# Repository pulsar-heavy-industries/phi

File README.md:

# What is this?

This repository hosts the source code, documentation and hardware design files for various [Pulsar Heavy Industries](http://pulsarheavyindustries.com/) projects.

There are currently 3 modules we are focusing on:
* [Cenx4](https://github.com/pulsar-heavy-industries/phi/tree/master/cenx4) - A small OLED+4 rotary encoders+other goodies modular controller.
* [Hyperion](https://github.com/pulsar-heavy-industries/phi/tree/master/hyperion) - A channel strip module, with an OLED display, 2 rotary encoders, 7 knobs, fader, and 8 LED-lit pushbuttons.
* [Narvi](https://github.com/pulsar-heavy-industries/phi/tree/master/narvi) - a 4 channel audio interface.

Our goal is to leverage technology from the last few years to push the DIY audio and MIDI controllers world forward. For more details see this series of [blog posts](http://rundste.in/tag/phi/).

# Showing off some of our prototypes

Cenx4:

Hyperion:

Narvi:

# Who is behind this?
Hi, I'm [Eran Rundstein](http://rundste.in/).

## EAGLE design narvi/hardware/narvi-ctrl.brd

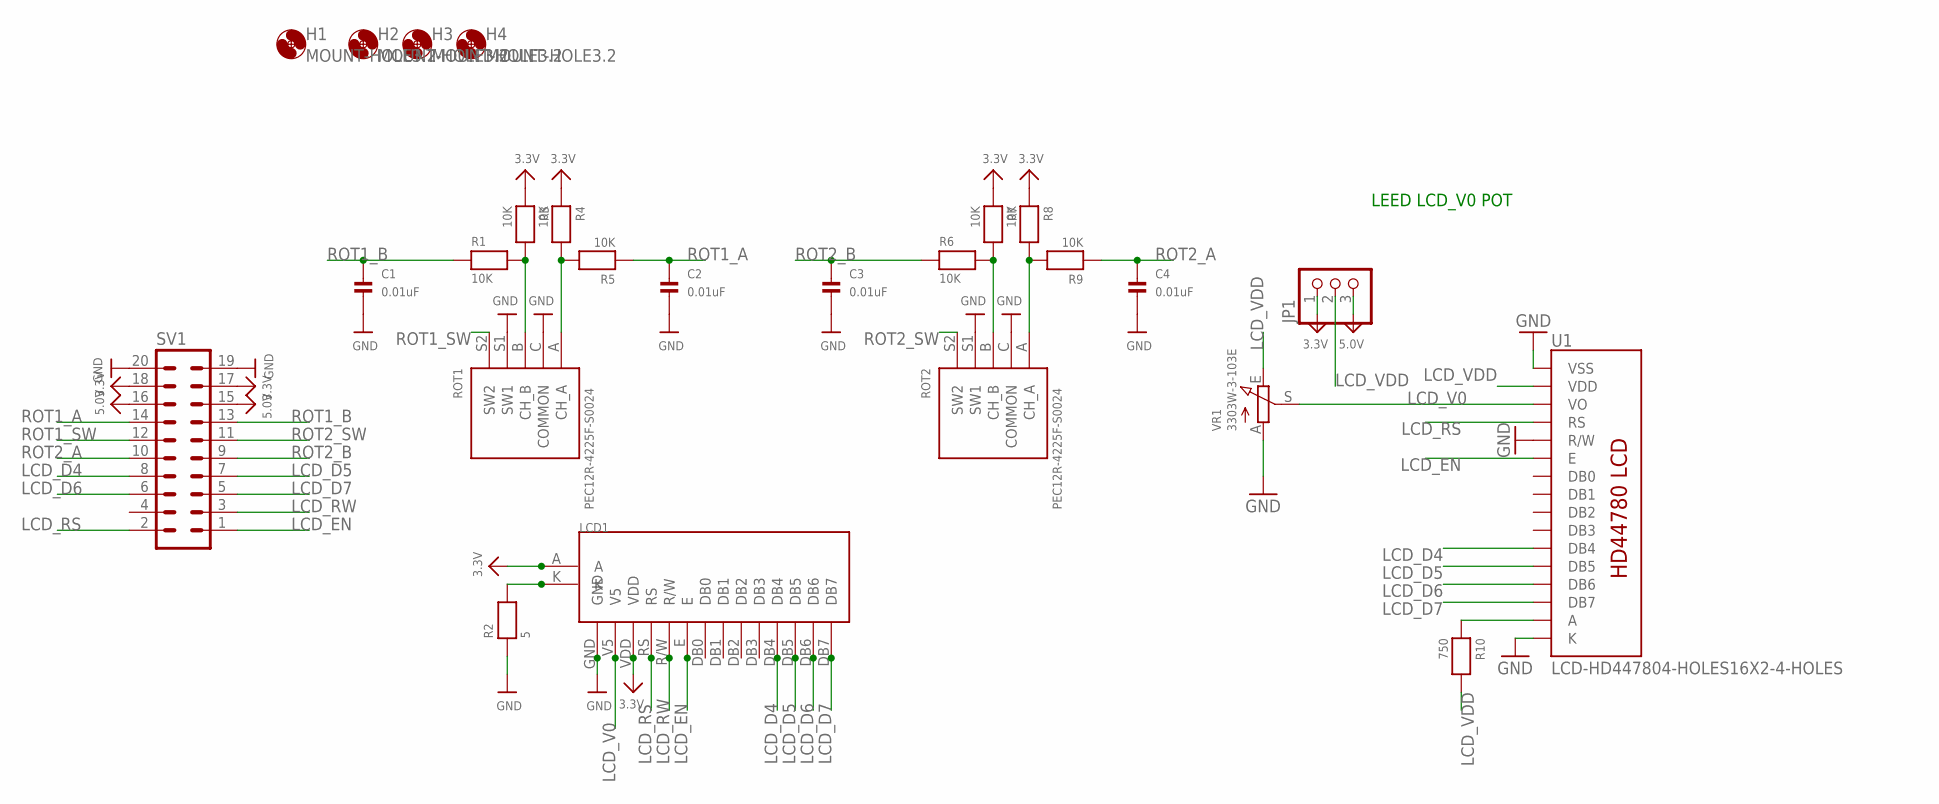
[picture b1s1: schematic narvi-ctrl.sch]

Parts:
C1, C2, C3, C4: 0.01uF; 0805
H1, H2, H3, H4: MOUNT-HOLE3.2; 3,2
JP1: PINHD-1X3; 1X03
LCD1: NHD-C0220AA-FSW-FTW
R1, R3, R4, R5, R6, R7, R8, R9: 10K; _0805
R2: 5; _0805
R10: 750; _0805
ROT1, ROT2: PEC12R-4225F-S0024; PEC111-4XXXK-SXXXX
SV1: ML203MSMT; ML20SMT; PARTNO D2520-6V0C-AR-WE
U1: LCD-HD447804-HOLES16X2-4-HOLES; LCD-16X2-4HOLES
VR1: 3303W-3-103E; TRIMPOT_BOURNS3MM

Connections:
3.3V: JP1.1, LCD1.A, LCD1.VDD, R3.1, R4.1, R7.1, R8.1, SV1.17, SV1.18
5.0V: JP1.3, SV1.15, SV1.16
GND: C1.2, C2.2, C3.2, C4.2, LCD1.GND, R2.1, ROT1.C (COMMON), ROT1.S1 (SW1), ROT2.C (COMMON), ROT2.S1 (SW1), SV1.19, SV1.20, U1.1 (VSS), U1.5 (R/W), U1.16 (K), VR1.A
LCD_D4: LCD1.DB4, SV1.8, U1.11 (DB4)
LCD_D5: LCD1.DB5, SV1.7, U1.12 (DB5)
LCD_D6: LCD1.DB6, SV1.6, U1.13 (DB6)
LCD_D7: LCD1.DB7, SV1.5, U1.14 (DB7)
LCD_EN: LCD1.E, SV1.1, U1.6 (E)
LCD_RS: LCD1.RS, SV1.2, U1.4 (RS)
LCD_RW: LCD1.R/W, SV1.3
LCD_V0: LCD1.V5, U1.3 (VO), VR1.S
LCD_VDD: JP1.2, R10.2, U1.2 (VDD), VR1.E
unnamed: LCD1.K, R2.2
unnamed: R10.1, U1.15 (A)
unnamed: R6.2, R7.2, ROT2.B (CH_B)
unnamed: R8.2, R9.2, ROT2.A (CH_A)
unnamed: R1.2, R3.2, ROT1.B (CH_B)
unnamed: R4.2, R5.2, ROT1.A (CH_A)
ROT1_A: C2.1, R5.1, SV1.14
ROT1_B: C1.1, R1.1, SV1.13
ROT1_SW: ROT1.S2 (SW2), SV1.12
ROT2_A: C4.1, R9.1, SV1.10
ROT2_B: C3.1, R6.1, SV1.9
ROT2_SW: ROT2.S2 (SW2), SV1.11

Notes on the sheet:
LEED LCD_V0 POT

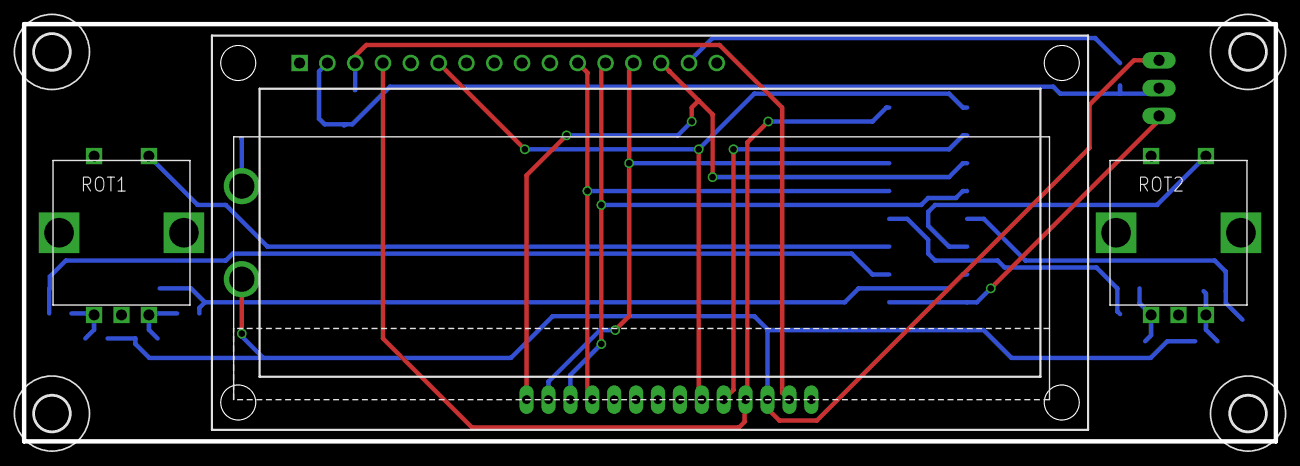
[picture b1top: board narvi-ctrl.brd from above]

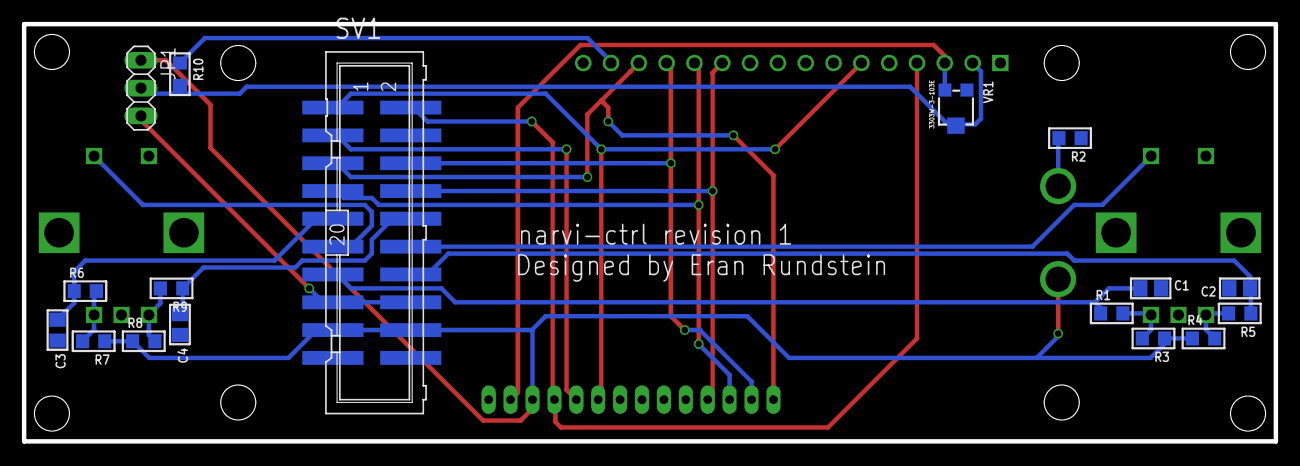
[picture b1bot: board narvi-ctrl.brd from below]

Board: 2 copper layers, 114.3 x 38.1 mm, 25 parts (17 on the bottom side), 24 nets.

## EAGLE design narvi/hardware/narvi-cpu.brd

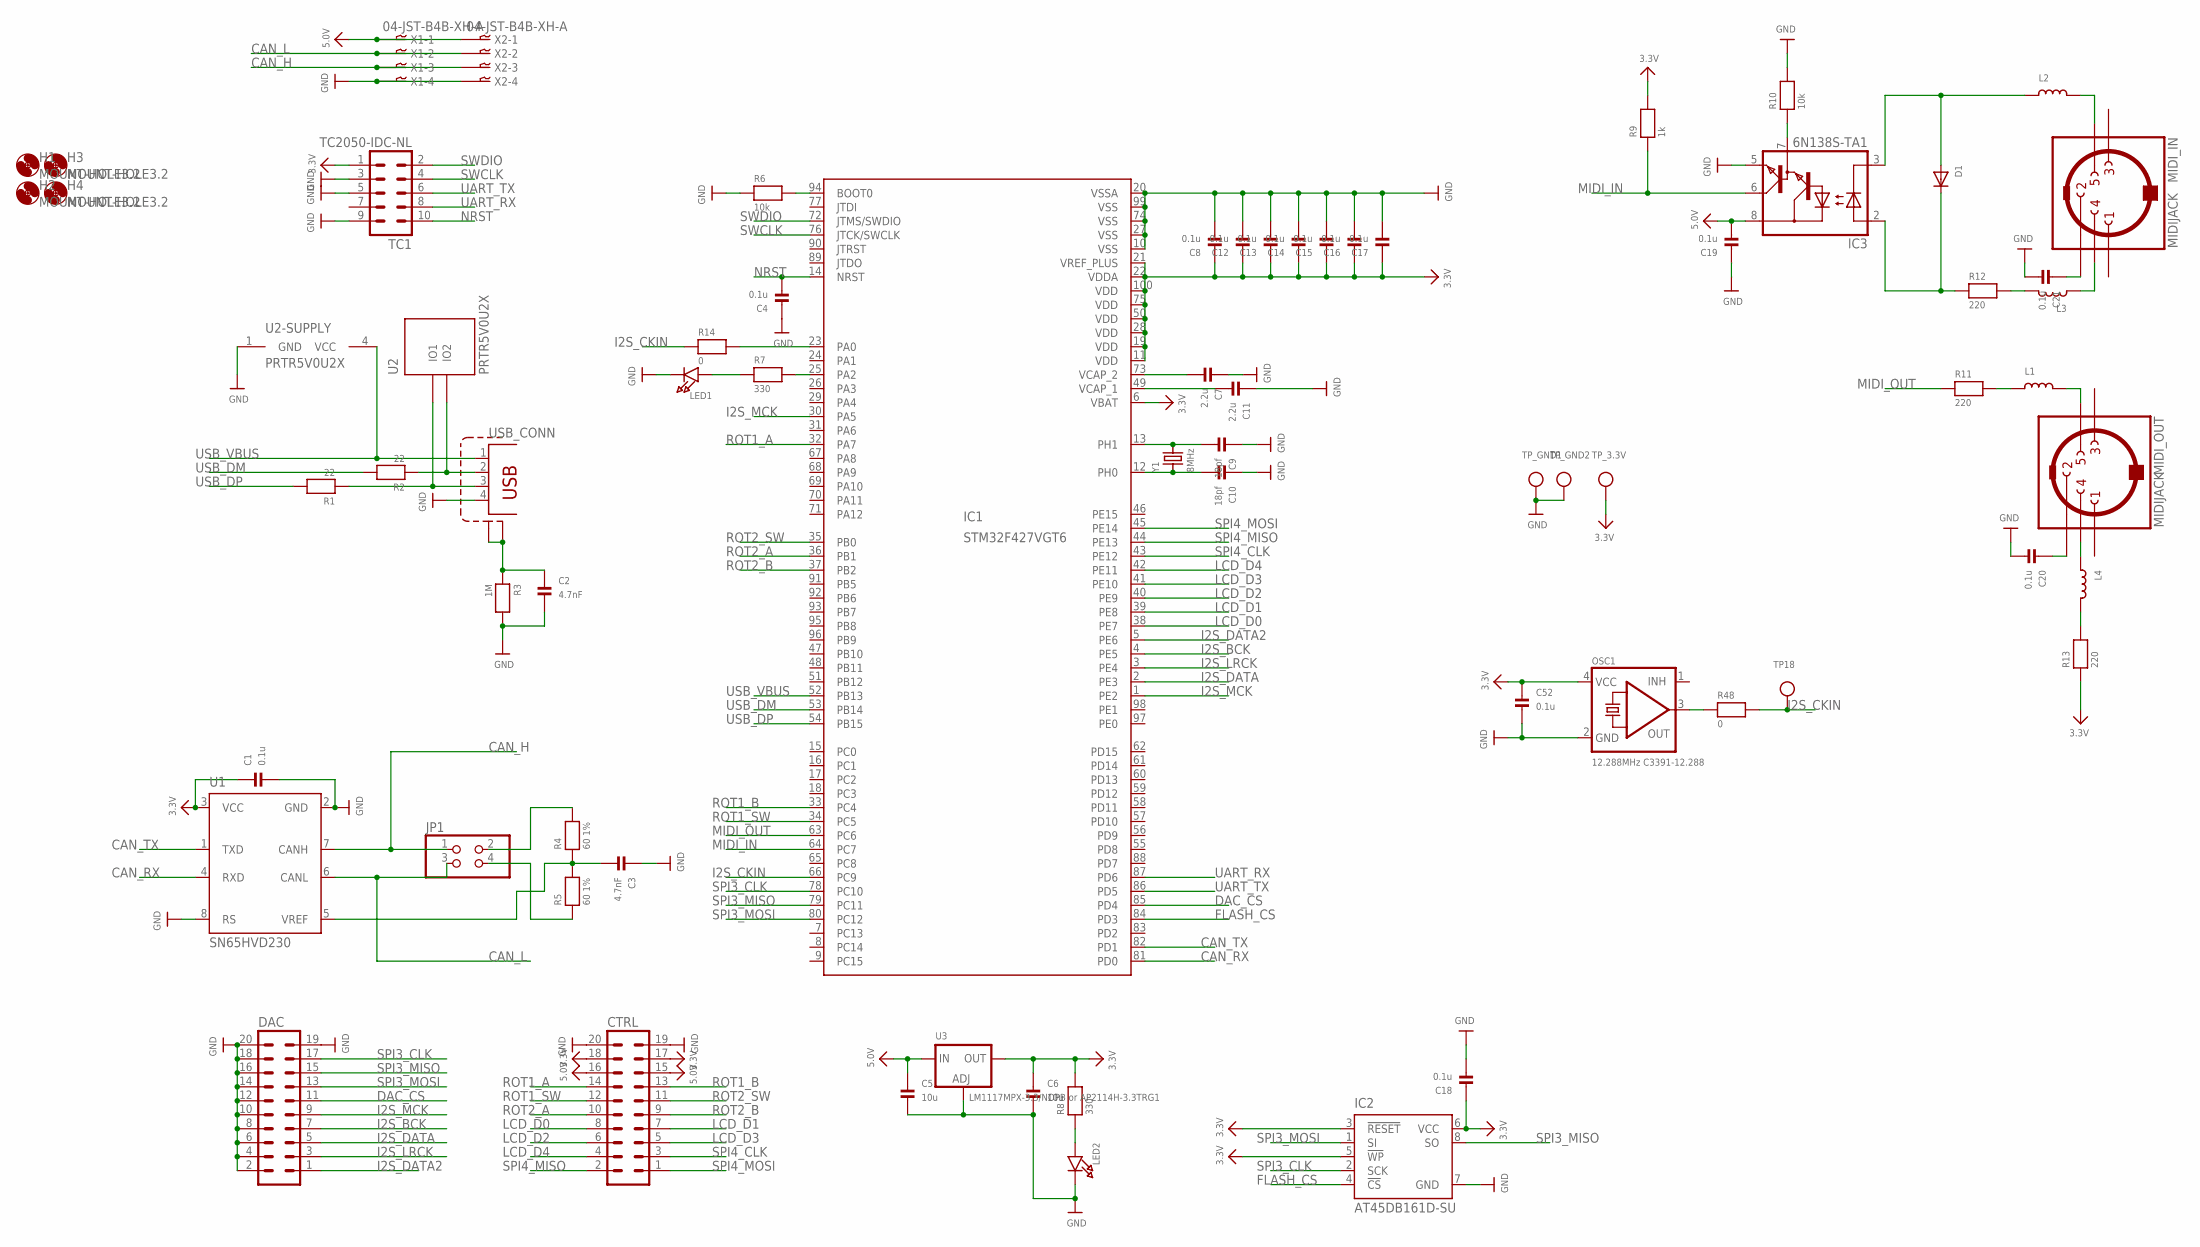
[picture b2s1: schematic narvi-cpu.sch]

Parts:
C1, C4, C8, C12, C13, C14, C15, C16, C17, C18, C19, C20, C21: 0.1u; 0603; PARTNO 0805DD104KAT2A
C2, C3: 4.7nF; 0805; PARTNO 885012207090
C5, C6: 10u; 0805; PARTNO 81-GRM21BR6YA106KE3L
C7, C11: 2.2u; 0805; PARTNO 581-08053D225MAT2A
C9, C10: 18pf; 0805; PARTNO C0805C180M3GACTU
C52: 0.1u; 0603
CTRL: ML20; PARTNO 61202021621
D1: DIODESOD-123; SOD-123; PARTNO MBR120
DAC: ML20; PARTNO 61202021621
H1, H2, H3, H4: MOUNT-HOLE3.2; 3,2
IC1: STM32F427VGT6; TQFP100; PARTNO STM32F427VGT6
IC2: AT45DB161D-SU; 8S2
IC3: 6N138S-TA1; SO8-GW300; PARTNO 6N138S
JP1: PINHD-2X2; 2X02
L1, L2, L3, L4: INDUCTOR0805; 0805; PARTNO 70-ILHB0805ER601V
LED1, LED2: LED0805; CHIPLED_0805; PARTNO 604-APT2012YC
MIDI_IN: MIDIJACK; CP-2350
MIDI_OUT: MIDIJACK; CP-2350
OSC1: 12.288MHz C3391-12.288; OSC_7X5MM
R1, R2: 22; 0805; MPN MF-RES-0603-22
R3: 1M; 0805; PARTNO AS08J1004ET
R4, R5: 60 1%; 0805; MPN MF-RES-0603-60.4
R6, R10: 10k; 0805; PARTNO RC0805FR-0710KL
R7, R8: 330; 0805; MPN MF-RES-0603-330
R9: 1k; 0805; PARTNO AS08J1001ET
R11, R12, R13: 220; 0805; PARTNO ERJ-6GEYJ221V
R14: 0; 0805; MPN MF-RES-0603-330
R48: 0; _0805
TC1: TC2050-IDC-NL
TP18: TESTPOINT0.1"; 1X01_ROUND
TP_3.3V: TESTPOINT0.1"; 1X01_ROUND
TP_GND1, TP_GND2: TESTPOINT0.1"; 1X01_ROUND
U1: SN65HVD230; SO8
U2: PRTR5V0U2X; SOT-143B
U3: LM1117MPX-3.3/NOPB or AP2114H-3.3TRG1; SOT223-R
USB: TE-292304-1
X1, X2: 04-JST-B4B-XH-A; B4B-XH
Y1: 8MHz; HC49UP; PARTNO ABLS2-8.000MHz-B1U-T

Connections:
3.3V: C1.1, C6.1, C8.1, C12.1, C13.1, C14.1, C15.1, C16.1, C17.1, C18.1, C52.1, CTRL.17, CTRL.18, IC1.6 (VBAT), IC1.11 (VDD), IC1.19 (VDD), IC1.21 (VREF_PLUS), IC1.22 (VDDA), IC1.28 (VDD), IC1.50 (VDD), IC1.75 (VDD), IC1.100 (VDD), IC2.3 (!RESET), IC2.5 (!WP), IC2.6 (VCC), OSC1.4 (VCC), R8.2, R9.2, R13.1, TC1.1, TP_3.3V.1, U1.3 (VCC), U3.2 (OUT)
5.0V: C5.1, C19.2, CTRL.15, CTRL.16, IC3.8 (VCC), U3.3 (IN), X1.P$1, X2.P$1
CAN_H: JP1.1, U1.7 (CANH), X1.P$3, X2.P$3
CAN_L: JP1.3, U1.6 (CANL), X1.P$2, X2.P$2
CAN_RX: IC1.81 (PD0), U1.4 (RXD)
CAN_TX: IC1.82 (PD1), U1.1 (TXD)
DAC_CS: DAC.11, IC1.85 (PD4)
FLASH_CS: IC1.84 (PD3), IC2.4 (!CS)
GND: C1.2, C2.2, C3.1, C4.1, C5.2, C6.2, C7.1, C8.2, C9.1, C10.1, C11.1, C12.2, C13.2, C14.2, C15.2, C16.2, C17.2, C18.2, C19.1, C20.2, C21.2, C52.2, CTRL.19, CTRL.20, DAC.2, DAC.4, DAC.6, DAC.8, DAC.10, DAC.12, DAC.14, DAC.16, DAC.18, DAC.19, DAC.20, IC1.10 (VSS), IC1.20 (VSSA), IC1.27 (VSS), IC1.74 (VSS), IC1.99 (VSS), IC2.7 (GND), IC3.5 (GND), LED1.C, LED2.C, OSC1.2 (GND), R3.2, R6.1, R10.2, TC1.3, TC1.5, TC1.9, TP_GND1.1, TP_GND2.1, U1.2 (GND), U1.8 (RS), U2.1 (GND), U3.1 (ADJ), USB.4, X1.P$4, X2.P$4
I2S_BCK: DAC.7, IC1.4 (PE5)
I2S_CKIN: IC1.66 (PC9), R14.1, R48.2, TP18.1
I2S_DATA: DAC.5, IC1.2 (PE3)
I2S_DATA2: DAC.1, IC1.5 (PE6)
I2S_LRCK: DAC.3, IC1.3 (PE4)
I2S_MCK: DAC.9, IC1.1 (PE2), IC1.30 (PA5)
LCD_D0: CTRL.8, IC1.38 (PE7)
LCD_D1: CTRL.7, IC1.39 (PE8)
LCD_D2: CTRL.6, IC1.40 (PE9)
LCD_D3: CTRL.5, IC1.41 (PE10)
LCD_D4: CTRL.4, IC1.42 (PE11)
MIDI_IN: IC1.64 (PC7), IC3.6 (VO), R9.1
MIDI_OUT: IC1.63 (PC6), R11.1
unnamed: IC1.94 (BOOT0), R6.2
unnamed: C11.2, IC1.49 (VCAP_1)
unnamed: C7.2, IC1.73 (VCAP_2)
unnamed: C9.2, IC1.13 (PH1), Y1.2
unnamed: C10.2, IC1.12 (PH0), Y1.1
unnamed: LED2.A, R8.1
unnamed: JP1.2, R4.2
unnamed: JP1.4, R5.1
unnamed: C3.2, R4.1, R5.2, U1.5 (VREF)
unnamed: IC1.25 (PA2), R7.2
unnamed: IC1.23 (PA0), R14.2
unnamed: LED1.A, R7.1
unnamed: L1.2, MIDI_OUT.5
unnamed: L1.1, R11.2
unnamed: L3.1, MIDI_IN.4
unnamed: D1.C, IC3.2 (A), R12.1
unnamed: R2.1, U2.3 (IO2), USB.2
unnamed: R1.1, U2.2 (IO1), USB.3
unnamed: C2.1, R3.1, USB.P$1 (S1), USB.P$2 (S2)
unnamed: D1.A, IC3.3 (C), L2.1
unnamed: IC3.7 (VB), R10.1
unnamed: C20.1, MIDI_OUT.2
unnamed: C21.1, MIDI_IN.2
unnamed: L2.2, MIDI_IN.5
unnamed: L3.2, R12.2
unnamed: L4.2, R13.2
unnamed: L4.1, MIDI_OUT.4
unnamed: OSC1.3 (OUT), R48.1
NRST: C4.2, IC1.14 (NRST), TC1.10
ROT1_A: CTRL.14, IC1.32 (PA7)
ROT1_B: CTRL.13, IC1.33 (PC4)
ROT1_SW: CTRL.12, IC1.34 (PC5)
ROT2_A: CTRL.10, IC1.36 (PB1)
ROT2_B: CTRL.9, IC1.37 (PB2)
ROT2_SW: CTRL.11, IC1.35 (PB0)
SPI3_CLK: DAC.17, IC1.78 (PC10), IC2.2 (SCK)
SPI3_MISO: DAC.15, IC1.79 (PC11), IC2.8 (SO)
SPI3_MOSI: DAC.13, IC1.80 (PC12), IC2.1 (SI)
SPI4_CLK: CTRL.3, IC1.43 (PE12)
SPI4_MISO: CTRL.2, IC1.44 (PE13)
SPI4_MOSI: CTRL.1, IC1.45 (PE14)
SWCLK: IC1.76 (JTCK/SWCLK), TC1.4
SWDIO: IC1.72 (JTMS/SWDIO), TC1.2
UART_RX: IC1.87 (PD6), TC1.8
UART_TX: IC1.86 (PD5), TC1.6
USB_DM: IC1.53 (PB14), R2.2
USB_DP: IC1.54 (PB15), R1.2
USB_VBUS: IC1.52 (PB13), U2.4 (VCC), USB.1

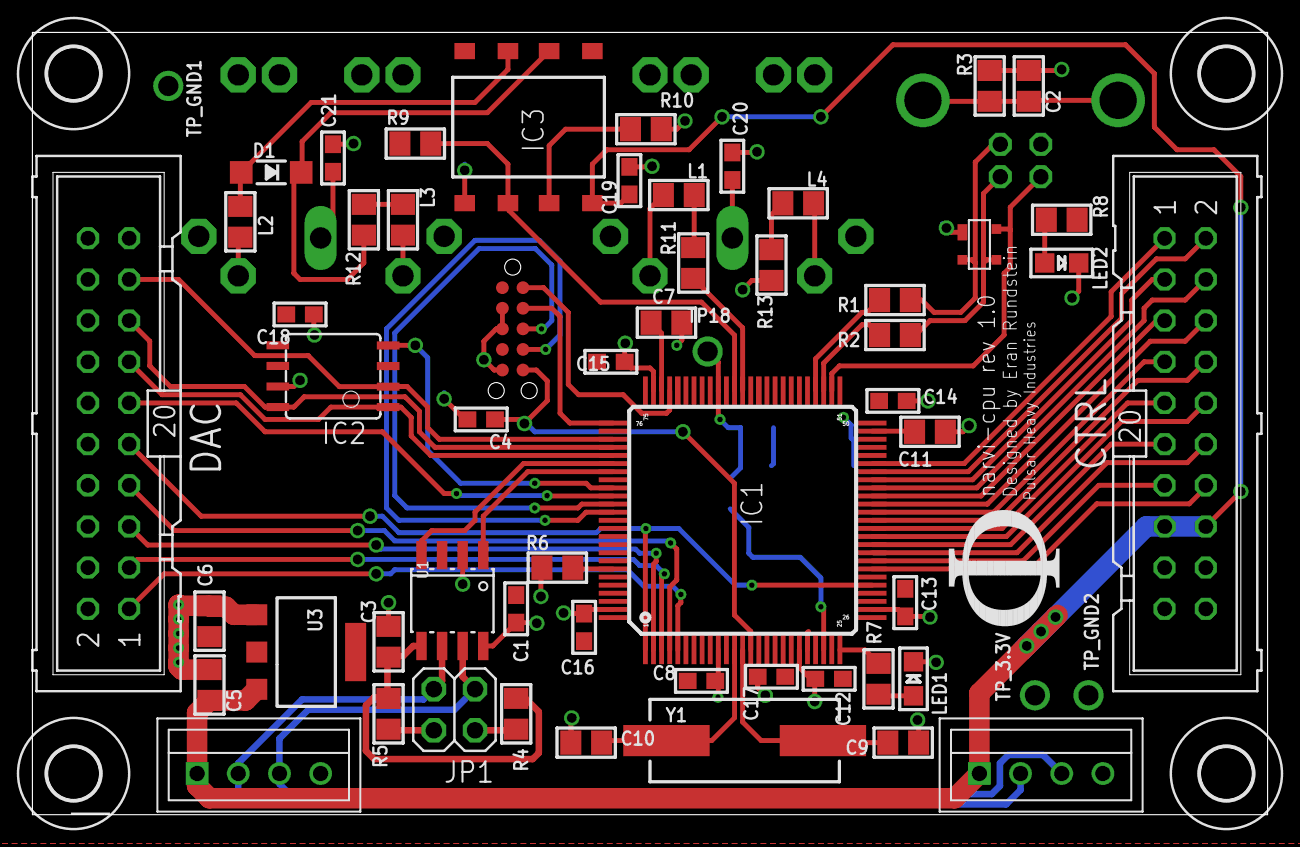
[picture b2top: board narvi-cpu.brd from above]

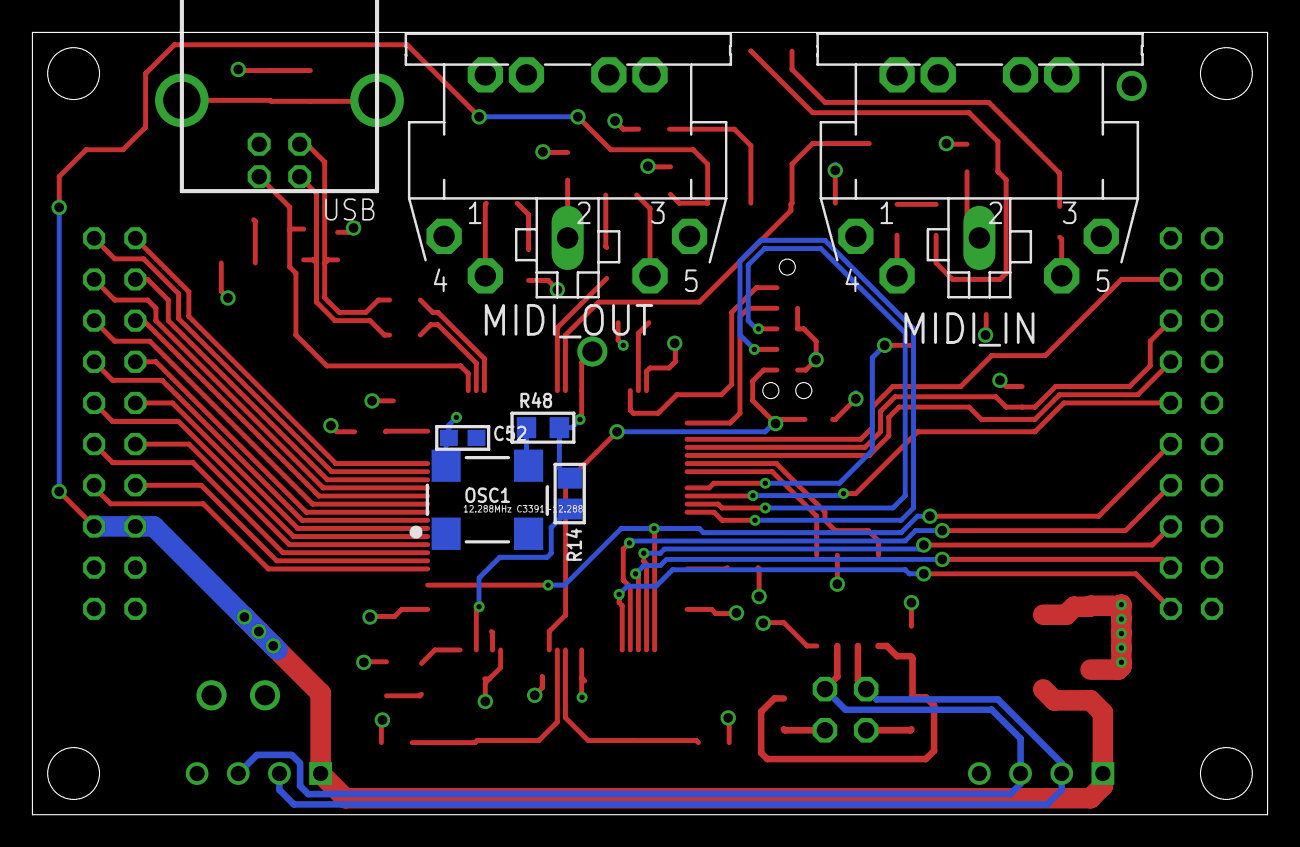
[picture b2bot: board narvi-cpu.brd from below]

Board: 2 copper layers, 76.2 x 48.3 mm, 69 parts (7 on the bottom side), 70 nets.

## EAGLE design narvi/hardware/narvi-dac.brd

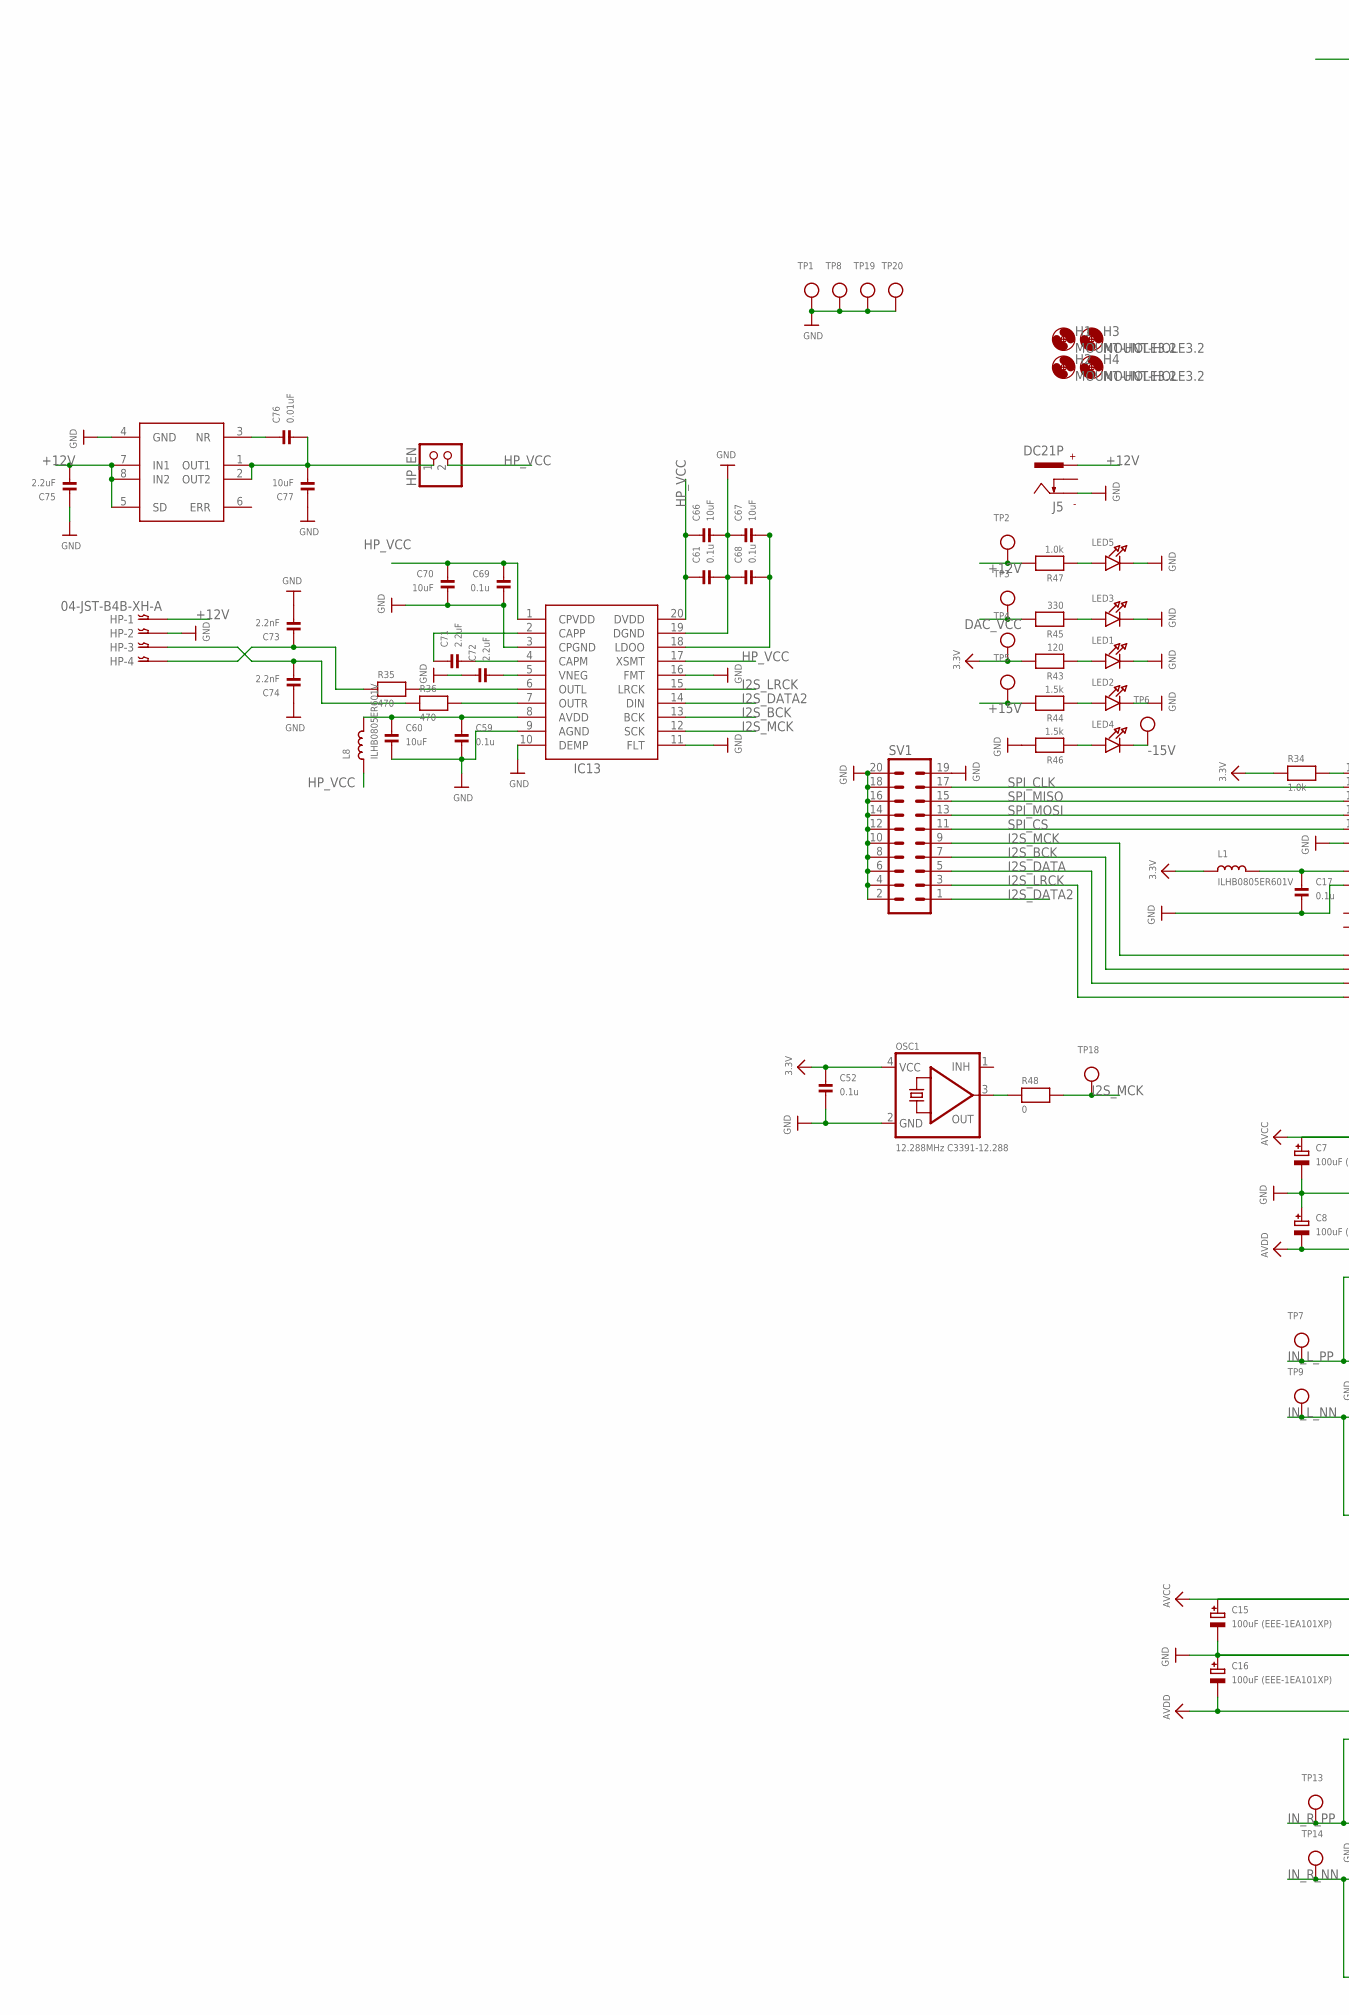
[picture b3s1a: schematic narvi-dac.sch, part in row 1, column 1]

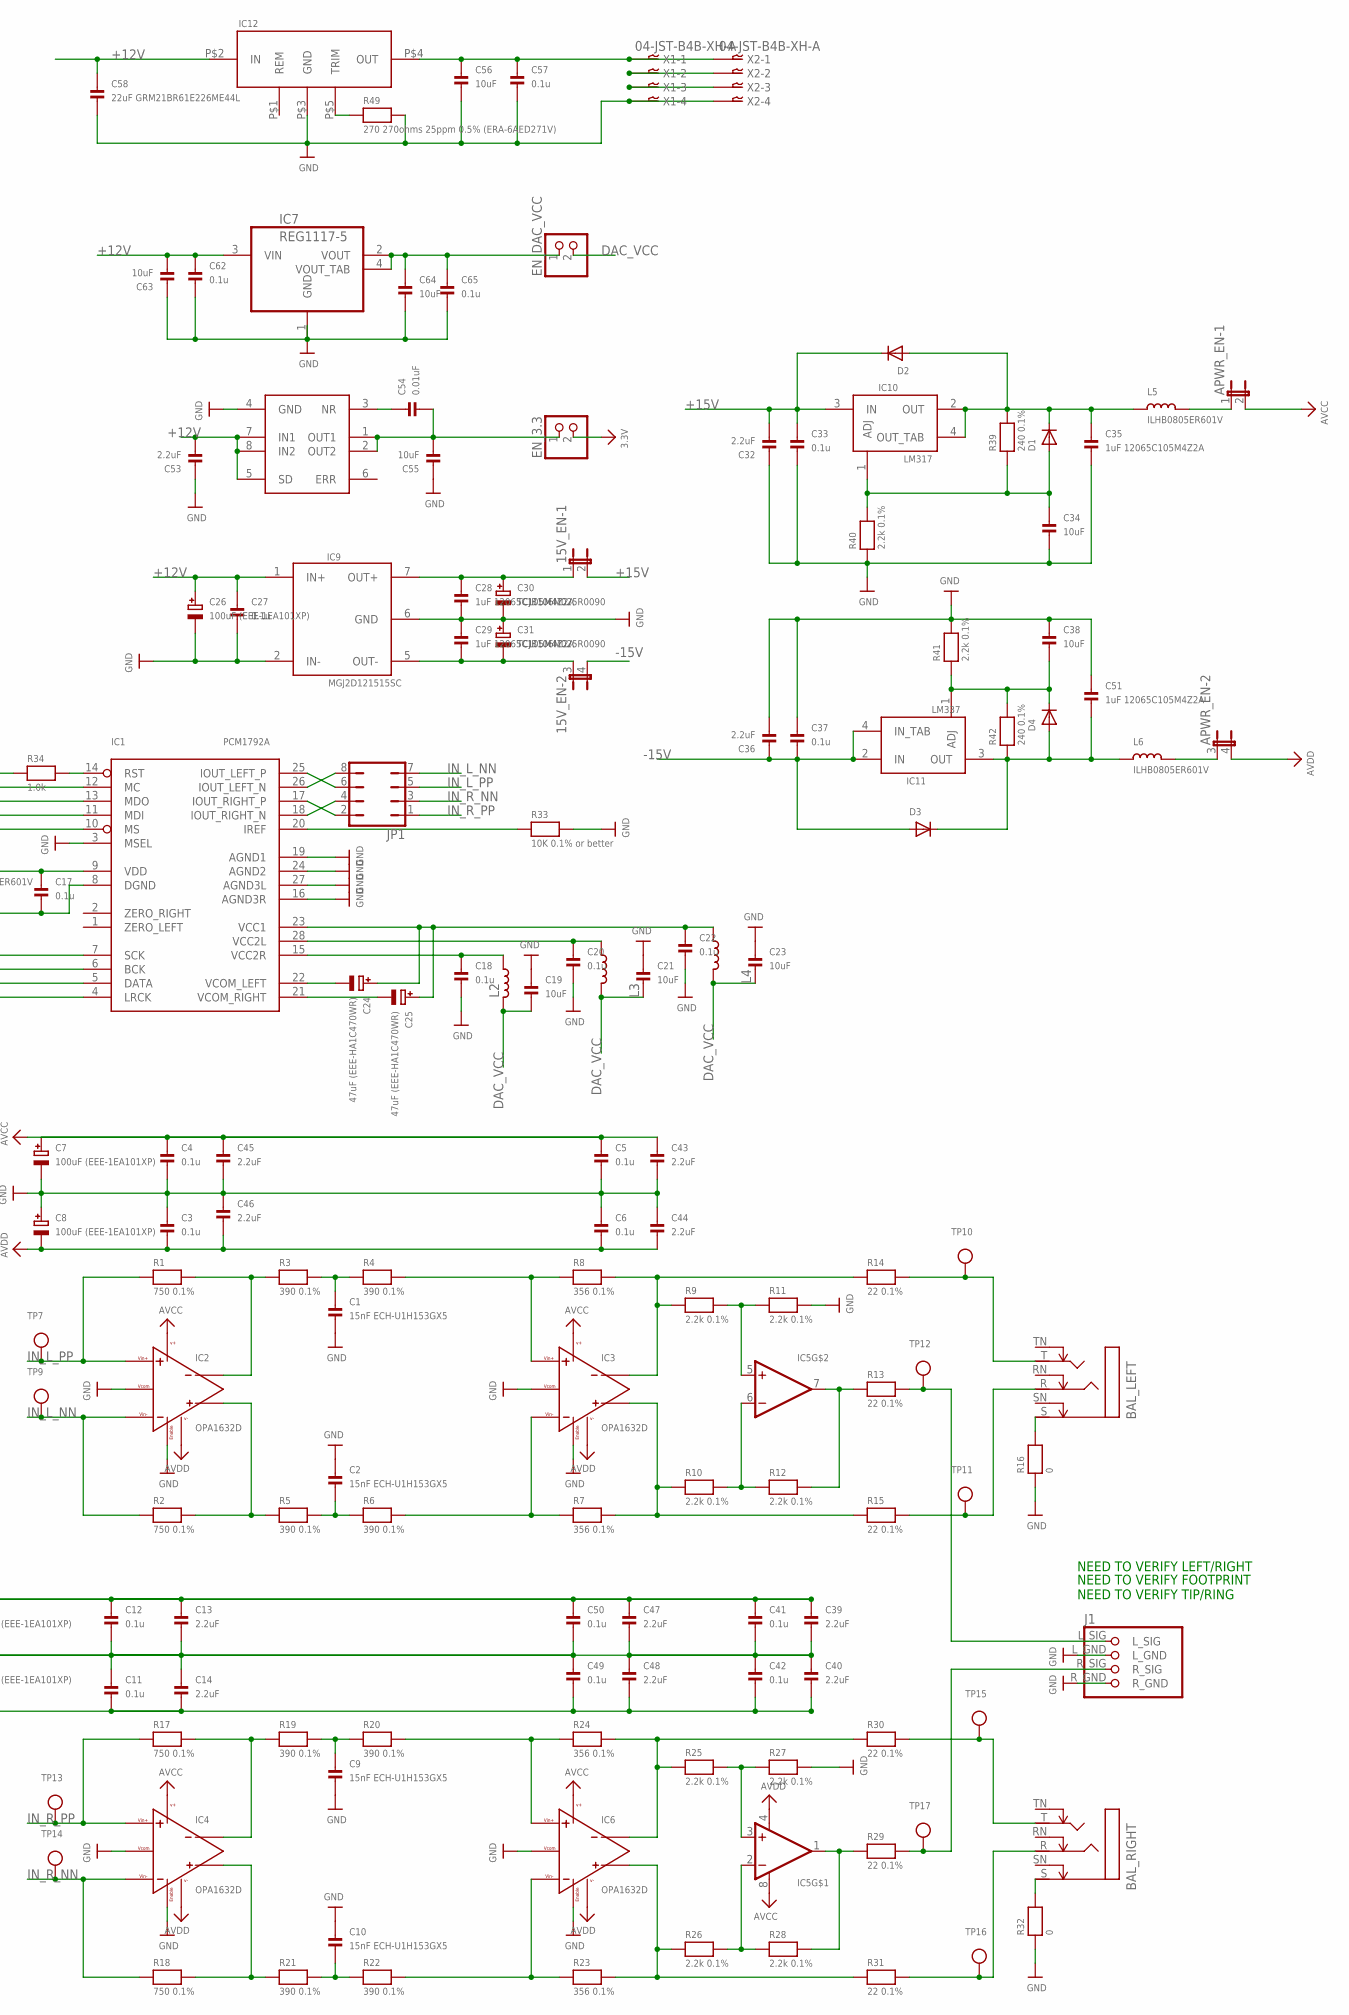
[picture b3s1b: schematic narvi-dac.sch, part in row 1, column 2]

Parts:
15V_EN: JP2QE; JP2Q
APWR_EN: JP2QE; JP2Q
BAL_LEFT: STEREOSW; NMJ6HCD2
BAL_RIGHT: STEREOSW; NMJ6HCD2
C1, C2, C9, C10: 15nF ECH-U1H153GX5; 1210
C3, C4, C5, C6, C11, C12, C17, C18, C20, C22, C27, C33, C37, C41, C42, C49, C50, C52, C57, C59, C61, C62, C65, C68, C69: 0.1u; 0603
C7, C8, C15, C16, C26: 100uF (EEE-1EA101XP); PANASONIC_D
C13, C14, C32, C36, C39, C40, C43, C44, C45, C46, C47, C48, C53, C71, C72, C75: 2.2uF; _0805
C19, C21, C23, C34, C38, C55, C56, C60, C63, C64, C66, C67, C70, C77: 10uF; 0805
C24, C25: 47uF (EEE-HA1C470WR); PANASONIC_C
C28, C29, C35, C51: 1uF 12065C105M4Z2A; 1206
C30, C31: TCJB106M025R0090; 1210POL
C54, C76: 0.01uF; 0603
C58: 22uF GRM21BR61E226ME44L; _0805
C73, C74: 2.2nF; _0805
D1, D2, D3, D4: DIODESOD-123; SOD-123
EN_3.3: HEADER-1X2; 1X02_OVAL
EN_DAC_VCC: HEADER-1X2; 1X02_OVAL
H1, H2, H3, H4: MOUNT-HOLE3.2; 3,2
HP: 04-JST-B4B-XH-A; B4B-XH
HP_EN: HEADER-1X2; 1X02_OVAL
IC1: PCM1792A; SSOP28
IC2, IC3, IC4, IC6: OPA1632D; SO08
IC5: LM4562; SOIC8_150MIL
IC7: REG1117-5; SOT223
IC8, IC14: ADP3301ARZ-3.3; SO08
IC9: MGJ2D121515SC; MURATA-MGJ2
IC10: LM317; SOT223
IC11: LM337; SOT223
IC12: MURATA_OKR-T/10-W12-C
IC13: PCM5102; TSSOP20
J1: CUI-RCJ-2123
J5: DC21P; CUI-PJ-102AH
JP1: JP4Q
L1, L2, L3, L4, L5, L6, L8: ILHB0805ER601V; _0805
LED1, LED2, LED3, LED4, LED5: LED0805; CHIPLED_0805
OSC1: 12.288MHz C3391-12.288; OSC_7X5MM
R1, R2, R17, R18: 750 0.1%; _0805
R3, R4, R5, R6, R19, R20, R21, R22: 390 0.1%; _0805
R7, R8, R23, R24: 356 0.1%; _0805
R9, R10, R11, R12, R25, R26, R27, R28, R40, R41: 2.2k 0.1%; _0805
R13, R14, R15, R29, R30, R31: 22 0.1%; _0805
R16, R32, R48: 0; _0805
R33: 10K 0.1% or better; _0805
R34, R47: 1.0k; _0805
R35, R36: 470; _0805
R39, R42: 240 0.1%; _0805
R43: 120; _0805
R44, R46: 1.5k; _0805
R45: 330; _0805
R49: 270 270ohms 25ppm 0.5% (ERA-6AED271V); _0805
SV1: ML20
TP1, TP2, TP3, TP4, TP5, TP6, TP7, TP8, TP9, TP10, TP11, TP12, TP13, TP14, TP15, TP16, TP17, TP18, TP19, TP20: TESTPOINT0.1"; 1X01_ROUND
X1, X2: 04-JST-B4B-XH-A; B4B-XH

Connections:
3.3V: C52.1, EN_3.3.2, L1.1, OSC1.4 (VCC), R34.1, R43.2, TP4.1
+12V: C26.+, C27.1, C53.2, C58.1, C62.1, C63.2, C75.2, HP.P$1, IC7.3 (VIN), IC8.5 (SD), IC8.7 (IN1), IC8.8 (IN2), IC9.1 (IN+), IC12.P$2 (IN), IC14.5 (SD), IC14.7 (IN1), IC14.8 (IN2), J5.+, R47.2, TP2.1
+15V: 15V_EN.2, C32.2, C33.1, D2.C, IC10.3 (IN), R44.2, TP5.1
-15V: 15V_EN.4 (2), C36.1, C37.2, D3.A, IC11.2 (IN), IC11.4 (IN_TAB), LED4.C, TP6.1
AVCC: APWR_EN.2, C4.1, C5.1, C7.+, C12.1, C13.1, C15.+, C39.1, C41.1, C43.1, C45.1, C47.1, C50.1, IC2.3 (V+), IC3.3 (V+), IC4.3 (V+), IC5.8 (V+), IC6.3 (V+)
AVDD: APWR_EN.4 (2), C3.2, C6.2, C8.-, C11.2, C14.2, C16.-, C40.2, C42.2, C44.2, C46.2, C48.2, C49.2, IC2.6 (V-), IC3.6 (V-), IC4.6 (V-), IC5.4 (V-), IC6.6 (V-)
CAN_H: X1.P$3, X2.P$3
CAN_L: X1.P$2, X2.P$2
DAC_VCC: C19.2, C21.2, C23.2, EN_DAC_VCC.2, L2.2, L3.2, L4.2, R45.2, TP3.1
GND: C1.2, C2.1, C3.1, C4.2, C5.2, C6.1, C7.-, C8.+, C9.2, C10.1, C11.1, C12.2, C13.2, C14.1, C15.-, C16.+, C17.2, C18.2, C19.1, C20.2, C21.1, C22.2, C23.1, C26.-, C27.2, C28.2, C29.1, C30.2- (-), C31.1+ (+), C32.1, C33.2, C34.2, C35.2, C36.2, C37.1, C38.1, C39.2, C40.1, C41.2, C42.1, C43.2, C44.1, C45.2, C46.1, C47.2, C48.1, C49.1, C50.2, C51.1, C52.2, C53.1, C55.1, C56.2, C57.2, C58.2, C59.2, C60.2, C61.2, C62.2, C63.1, C64.2, C65.2, C66.2, C67.1, C68.1, C69.2, C70.2, C72.1, C73.2, C74.1, C75.1, C77.1, HP.P$2, IC1.3 (MSEL), IC1.8 (DGND), IC1.16 (AGND3R), IC1.19 (AGND1), IC1.24 (AGND2), IC1.27 (AGND3L), IC2.2 (VCOM), IC2.7 (ENABLE), IC3.2 (VCOM), IC3.7 (ENABLE), IC4.2 (VCOM), IC4.7 (ENABLE), IC6.2 (VCOM), IC6.7 (ENABLE), IC7.1 (GND), IC8.4 (GND), IC9.2 (IN-), IC9.6 (GND), IC12.P$3 (GND), IC13.3 (CPGND), IC13.9 (AGND), IC13.10 (DEMP), IC13.11 (FLT), IC13.16 (FMT), IC13.19 (DGND), IC14.4 (GND), J1.L_GND, J1.R_GND, J5.-, LED1.C, LED2.C, LED3.C, LED5.C, OSC1.2 (GND), R11.2, R16.1, R27.2, R32.1, R33.2, R40.1, R41.2, R46.2, R49.2, SV1.2, SV1.4, SV1.6, SV1.8, SV1.10, SV1.12, SV1.14, SV1.16, SV1.18, SV1.19, SV1.20, TP1.1, TP8.1, TP19.1, TP20.1, X1.P$4, X2.P$4
HP_L_OUT: C73.1, HP.P$4, R35.1
HP_R_OUT: C74.2, HP.P$3, R36.1
HP_VCC: C61.1, C66.1, C69.1, C70.1, HP_EN.2, IC13.1 (CPVDD), IC13.17 (XSMT), IC13.20 (DVDD), L8.1
I2S_BCK: IC1.6 (BCK), IC13.13 (BCK), SV1.7
I2S_DATA: IC1.5 (DATA), SV1.5
I2S_DATA2: IC13.14 (DIN), SV1.1
I2S_LRCK: IC1.4 (LRCK), IC13.15 (LRCK), SV1.3
I2S_MCK: IC1.7 (SCK), IC13.12 (SCK), R48.2, SV1.9, TP18.1
IN_L_NN: IC2.1 (VIN-), JP1.7, R2.1, TP9.1
IN_L_PP: IC2.8 (VIN+), JP1.5, R1.1, TP7.1
IN_R_NN: IC4.1 (VIN-), JP1.3, R18.1, TP14.1
IN_R_PP: IC4.8 (VIN+), JP1.1, R17.1, TP13.1
unnamed: IC2.5 (VOUT-), R1.2, R3.1
unnamed: IC2.4 (VOUT+), R2.2, R5.1
unnamed: C1.1, R3.2, R4.1
unnamed: C2.2, R5.2, R6.1
unnamed: IC3.8 (VIN+), R4.2, R8.1
unnamed: IC3.1 (VIN-), R6.2, R7.1
unnamed: IC1.17 (IOUT_RIGHT_P), JP1.2
unnamed: IC1.18 (IOUT_RIGHT_N), JP1.4
unnamed: IC5.5 (+IN), R9.2, R11.1
unnamed: IC5.6 (-IN), R10.2, R12.1
unnamed: IC5.7 (OUT), R12.2, R13.1
unnamed: J1.L_SIG, R13.2, TP12.1
unnamed: BAL_LEFT.S, R16.2
unnamed: BAL_LEFT.T, R14.2, TP10.1
unnamed: BAL_LEFT.R, R15.2, TP11.1
unnamed: IC4.5 (VOUT-), R17.2, R19.1
unnamed: IC4.4 (VOUT+), R18.2, R21.1
unnamed: C9.1, R19.2, R20.1
unnamed: C10.2, R21.2, R22.1
unnamed: IC6.8 (VIN+), R20.2, R24.1
unnamed: IC6.1 (VIN-), R22.2, R23.1
unnamed: IC1.26 (IOUT_LEFT_N), JP1.8
unnamed: IC1.25 (IOUT_LEFT_P), JP1.6
unnamed: IC5.3 (+IN), R25.2, R27.1
unnamed: IC5.2 (-IN), R26.2, R28.1
unnamed: J1.R_SIG, R29.2, TP17.1
unnamed: BAL_RIGHT.S, R32.2
unnamed: BAL_RIGHT.T, R30.2, TP15.1
unnamed: BAL_RIGHT.R, R31.2, TP16.1
unnamed: C56.1, C57.1, IC12.P$4 (OUT), X1.P$1, X2.P$1
unnamed: OSC1.3 (OUT), R48.1
unnamed: IC12.P$5 (TRIM), R49.1
unnamed: IC5.1 (OUT), R28.2, R29.1
unnamed: IC1.20 (IREF), R33.1
unnamed: C18.1, IC1.15 (VCC2R), L2.1
unnamed: C17.1, IC1.9 (VDD), L1.2
unnamed: C20.1, IC1.28 (VCC2L), L3.1
unnamed: C22.1, C24.+, C25.+, IC1.23 (VCC1), L4.1
unnamed: C24.-, IC1.22 (VCOM_LEFT)
unnamed: C25.-, IC1.21 (VCOM_RIGHT)
unnamed: IC1.14 (RST), R34.2
unnamed: C59.1, C60.1, IC13.8 (AVDD), L8.2
unnamed: C67.2, C68.2, IC13.18 (LDOO)
unnamed: C71.1, IC13.2 (CAPP)
unnamed: C54.2, C55.2, EN_3.3.1, IC8.1 (OUT1), IC8.2 (OUT2)
unnamed: C54.1, IC8.3 (NR)
unnamed: 15V_EN.3 (1), C29.2, C31.2- (-), IC9.5 (OUT-)
unnamed: 15V_EN.1, C28.1, C30.1+ (+), IC9.7 (OUT+)
unnamed: C64.1, C65.1, EN_DAC_VCC.1, IC7.2 (VOUT), IC7.4 (VOUT_TAB)
unnamed: APWR_EN.1, L5.2
unnamed: C35.1, D1.C, D2.A, IC10.2 (OUT), IC10.4 (OUT_TAB), L5.1, R39.2
unnamed: C34.1, D1.A, IC10.1 (ADJ), R39.1, R40.2
unnamed: APWR_EN.3 (1), L6.2
unnamed: LED1.A, R43.1
unnamed: C51.2, D3.C, D4.A, IC11.3 (OUT), L6.1, R42.1
unnamed: C38.2, D4.C, IC11.1 (ADJ), R41.1, R42.2
unnamed: LED3.A, R45.1
unnamed: LED2.A, R44.1
unnamed: LED4.A, R46.1
unnamed: LED5.A, R47.1
unnamed: C71.2, IC13.4 (CAPM)
unnamed: C72.2, IC13.5 (VNEG)
unnamed: C76.1, IC14.3 (NR)
unnamed: IC13.6 (OUTL), R35.2
unnamed: IC13.7 (OUTR), R36.2
unnamed: C76.2, C77.2, HP_EN.1, IC14.1 (OUT1), IC14.2 (OUT2)
OUT_L_NN: IC3.4 (VOUT+), R7.2, R10.1, R15.1
OUT_L_PP: IC3.5 (VOUT-), R8.2, R9.1, R14.1
OUT_R_NN: IC6.4 (VOUT+), R23.2, R26.1, R31.1
OUT_R_PP: IC6.5 (VOUT-), R24.2, R25.1, R30.1
SPI_CLK: IC1.12 (MC), SV1.17
SPI_CS: IC1.10 (MS), SV1.11
SPI_MISO: IC1.13 (MDO), SV1.15
SPI_MOSI: IC1.11 (MDI), SV1.13

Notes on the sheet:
NEED TO VERIFY FOOTPRINT NEED TO VERIFY TIP/RING
NEED TO VERIFY LEFT/RIGHT

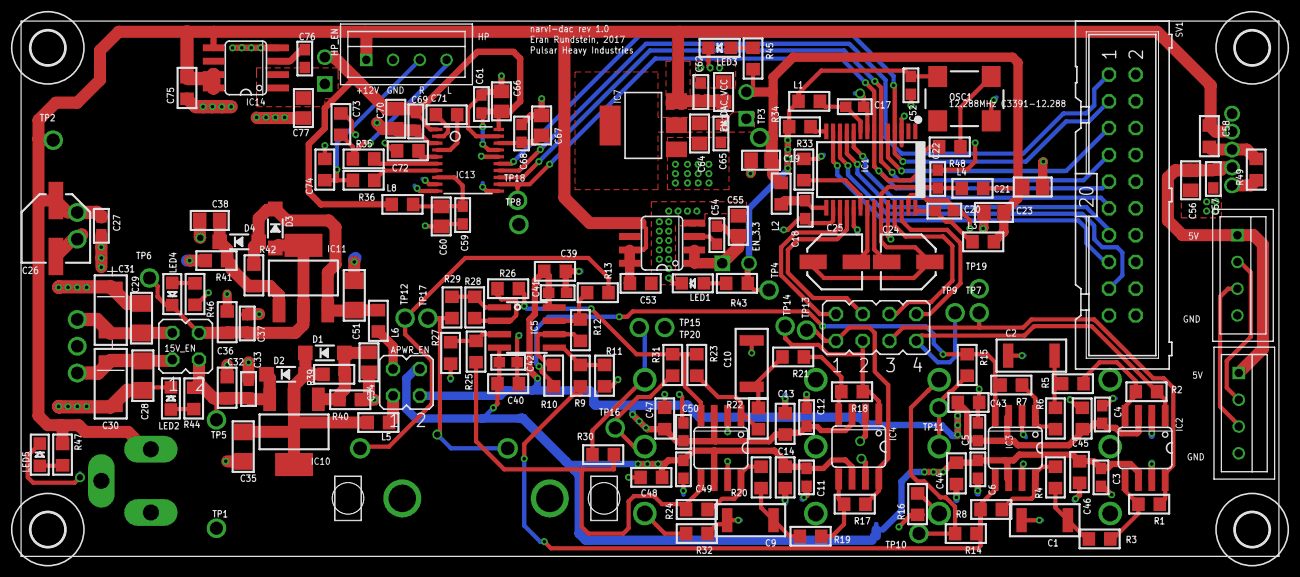
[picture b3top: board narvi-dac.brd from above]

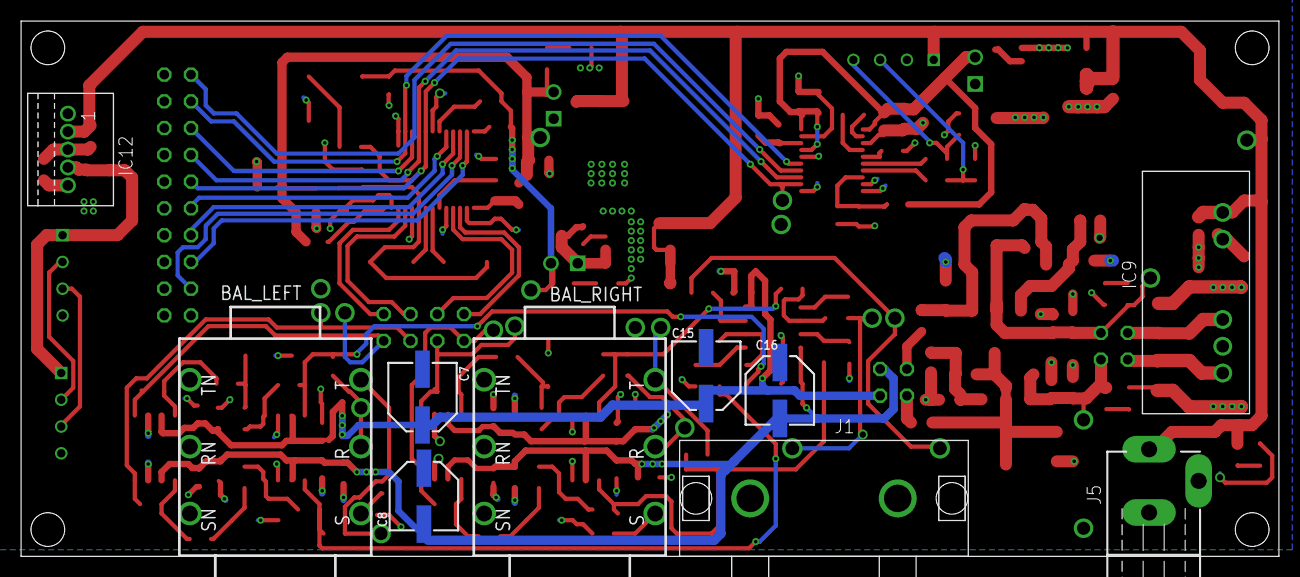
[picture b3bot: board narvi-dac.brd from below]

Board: 2 copper layers, 119.4 x 50.8 mm, 193 parts (10 on the bottom side), 96 nets.

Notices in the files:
parts and their libraries:
microbuilder: This work is placed in the public domain, and may be freely used for commercial and non-commercial work with the following conditions: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
SparkFun-Capacitors: Licensing: Creative Commons ShareAlike 4.0 International - https://creativecommons.org/licenses/by-sa/4.0
